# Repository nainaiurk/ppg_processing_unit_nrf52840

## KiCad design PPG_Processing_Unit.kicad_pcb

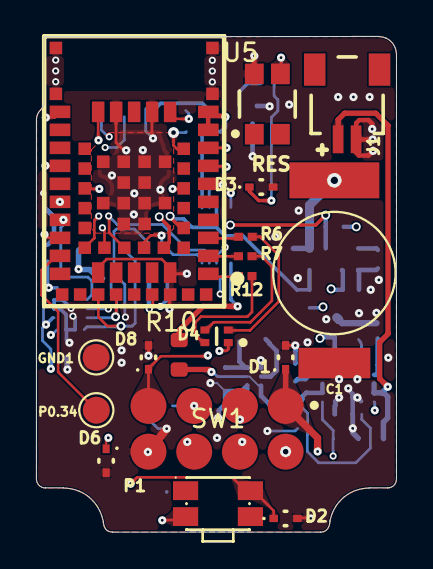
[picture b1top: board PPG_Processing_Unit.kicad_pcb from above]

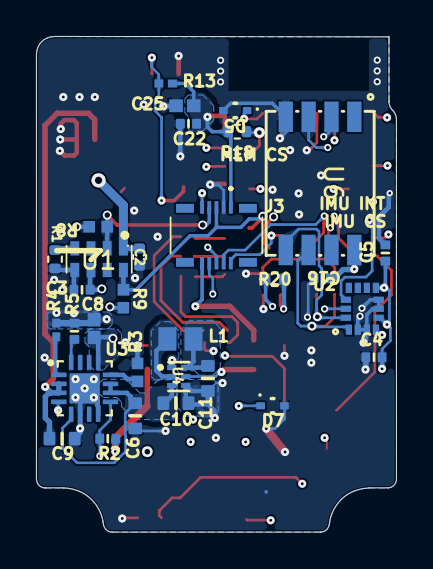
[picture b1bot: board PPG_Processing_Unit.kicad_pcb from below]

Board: 6 copper layers, 20.0 x 27.5 mm, 49 parts (31 on the bottom side), 41 nets.

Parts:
C1: .22F-SUPERCAP; DSK-RADIAL-6.8MM
C2: 0.1uF; C_0402_1005Metric
C3: Capacitor 0.1uF 0402; CAPC0402(1005)60_L
C4, C5, C16, C22: Capacitor 100nF +/-20% 25V 0402; CAPC0402(1005)60_L
C6, C9, C10, C11: Capacitor 4.7µF +/-20% 10V 0603; CAPC0603(1608)100_L
C8, C25: Capacitor 1 uF +/- 10% 6.3 V 0402; CAPC1005X55X25ML05T10
D1, D2, D3, D5, D6, D7, D8: ESD5Z3.3T1G; ONSC-SOD-523-2-502-01_V
D4: APHF1608LSEEQBDZGKC; FP-APHF1608LSEEQBDZGKC-MFG
GND1: TestPoint; TestPoint_Pad_D1.5mm
J1: SM02B-SRSS-TB(LF)(SN); FP-SM02B-SRSS-TB_LF_SN-0
J3: 51338-9873; 513389873
L1: LQM21PN2R2MGHL; FP-LQM21PH_G0-IPC_C
P0.34: TestPoint; TestPoint_Pad_D1.5mm
P1: 814-22-008-30-001101; 814-22-008-30-001101-Footprint-1
R1: 10K; R_0402_1005Metric
R2: Resistor 100K +/-1 % 0402 63 mW; RESC0402(1005)_L
R3, R8, R9: Resistor 4k7 +/-1% 0402 63 mW; RESC1005X40X25ML05T05
R4, R13: 10k; RESC1005X40X25LL05T10
R5: Resistor 12K +/-1 % 0402 63 mW; RESC0402(1005)_L
R6: 680R; RESC1005X40X25LL05T10
R7, R12: 180R; RESC1005X40X25LL05T10
R10: 0Ω; R_0603
R18: 4.7K; R_0402_1005Metric
R20: 22R; R_0402_1005Metric
SW1: EVQP7A01P; C79167_SW-SMD_EVQP7A01P
SW2: EVP-AAU02Q; FP-EVP-AAU02Q-MFG
U1: RV-3032-C7-32.768KHZ-2.5PPM-TA-QA; C5366550_DFN-8_L3_2-W1_5-P0_9-BL
U2: ISM330DHCXTR; FP-LGA-14L-DM00249496-MFG
U3: BQ24232HARGTR; QFN50P300X300X100-17N
U4: TPS62233DRYR; C2650320_SON-6_L1_5-W1_0-P0_50-BL
U5: NINA-B306; C6127317_LGA-60_L15_0-W10_0-NINA-B406-00B
U6: MKDV32GCL-STP; C7500179_LGA-8_L6_0-W8_0-P1_27-TL

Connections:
3V0: C3.2, C4.2, C5.2, C11.2, C16.2, C22.2, C25.2, D1.1 (K), D4.1 (COMMON_ANODE), J3.1, L1.2, P1.1, R2.2, R8.2, R9.2, R13.2, R18.2, SW1.2, U1.6 (VDD), U2.5 (VDDIO), U2.8 (VDD), U4.6 (FB), U5.9 (VCC_IO), U5.10 (VCC), U6.8 (VDD)
5V: C8.2, P1.2, U3.13 (IN)
/U_MCU/BATT_CE: U3.4 (~CE), U5.23 (GPIO_23/P0.29)
/U_MCU/FRAM_CS: R18.1, U5.36 (GPIO_36/P1.02), U6.2 (DAT3)
/U_MCU/GPIO: D8.1 (K), P1.7, U5.7 (GPIO_7/P0.25)
/U_MCU/IMU_CS: U2.12 (CS), U5.22 (GPIO_22/P1.13)
/U_MCU/IMU_INT: U2.4 (INT1), U5.21 (GPIO_21/P1.12)
/U_MCU/LED_BLUE: R7.2, U5.2 (GPIO_2/P0.14)
/U_MCU/LED_GREEN: R12.2, U5.1 (GPIO_1/P0.13)
/U_MCU/LED_RED: R6.2, U5.3 (GPIO_3/P0.15)
/U_MCU/MISO: U2.1 (SDO/SA0), U5.49 (GPIO_49/P0.22/QSPI_D2), U6.6 (DAT0)
/U_MCU/MOSI: U2.14 (SDA), U5.50 (GPIO_50/P0.20/QSPI_D0), U6.5 (CMD)
/U_MCU/PU_ANALOG: J3.9, U5.16 (GPIO_16/P0.03)
/U_MCU/PU_GPIO0: J3.8, U5.42 (GPIO_42/P0.26)
/U_MCU/PU_GPIO1: J3.6, U5.43 (GPIO_43/P0.06)
/U_MCU/PU_GPIO2: J3.4, U5.44 (GPIO_44/P0.27)
/U_MCU/PU_GPIO3: J3.2, U5.45 (GPIO_45/P0.07/TRACE_CLK)
/U_MCU/RESET: D3.1 (K), P1.6, R13.1, SW2.2?, U5.19 (RESET_N)
/U_MCU/SCK: R20.1, U2.13 (SCL), U5.52 (GPIO_52/P0.19/QSPI_CLK)
/U_MCU/SCL: J3.5, R9.1, U1.8 (SCL), U5.32 (GPIO_32/P0.11/TRACE_D2)
/U_MCU/SDA: J3.7, R8.1, U1.2 (SDA), U5.46 (GPIO_46/P0.12/TRACE_D1)
/U_MCU/SWCLK: D5.1 (K), P1.4, U5.11 (SWDCLK)
/U_MCU/SWDIO: D6.1 (K), P1.3, U5.15 (SWDIO)
/U_MCU/SWO: D7.1 (K), P1.5, U5.8 (GPIO_8/P1.00/TRACE_D0/SWO)
/U_MCU/USER_SWITCH: D2.1 (K), SW1.1', U5.34 (GPIO_34/P1.08)
/U_Power/CHG#: R2.1, U3.9 (~CHG), U5.39 (GPIO_39/P1.11)
/U_Sensors/VBACKUP: C1.+, C2.1, U1.1 (VBACKUP)
/U_UserInterface/BLUE: D4.3 (Blue_C), R7.1
/U_UserInterface/GREEN: D4.4 (Green_C), R12.1
/U_UserInterface/RED: D4.2 (Red_C), R6.1
GND: C1.-, C2.2, C3.1, C4.1, C5.1, C6.1, C8.1, C9.1, C10.1, C11.1, C16.1, C22.1, C25.1, D1.2 (A), D2.2 (A), D3.2 (A), D5.2 (A), D6.2 (A), D7.2 (A), D8.2 (A), GND1.1 (1_1), J1.1, J3.3, P1.8, R1.1, R3.1, R4.1, R5.1, SW2.1?, U1.5 (VSS), U2.2 (SDx), U2.3 (SCx), U2.6 (GND), U2.7 (GND), U3.6 (EN1), U3.8 (VSS), U3.17 (THERMALPAD), U4.1 (MODE), U4.4 (GND), U5.6 (GND6), U5.12 (GND12), U5.14 (GND14), U5.26 (GND26), U5.30 (GND30), U5.53 (GND53), U5.56 (EGP56), U5.57 (EGP57), U5.58 (EGP58), U5.59 (EGP59), U5.60 (EGP60), U6.4 (GND)
unnamed: C9.2, J1.2, U3.2 (BAT), U3.3 (BAT)
unnamed: J3.10, R10.1
unnamed: R1.2, U1.4 (EVI)
unnamed: R3.2, U3.12 (ILIM)
unnamed: R5.2, U3.16 (ISET)
unnamed: R4.2, U3.1 (TS)
unnamed: L1.1, U4.2 (SW)
unnamed: P0.34.1 (1_1), U5.24 (GPIO_24/P0.30)
unnamed: R20.2, U6.3 (CLK)
SYS_PWR: C6.2, C10.2, R10.2, U3.5 (EN2), U3.10 (OUT), U3.11 (OUT), U4.3 (VIN), U4.5 (EN)

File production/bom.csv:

Designator,Footprint,Quantity,Value,LCSC Part #
"C10, C11, C6, C9",CAPC0603(1608)100_L,4,Capacitor 4.7µF +/-20% 10V 0603,C389010 
"C16, C22, C4, C5",CAPC0402(1005)60_L,4,Capacitor 100nF +/-20% 25V 0402,C426067 
C2,0402,1,0.1uF,C426067 
"C25, C8",CAPC1005X55X25ML05T10,2,Capacitor 1 uF +/- 10% 6.3 V 0402,C88945 
C3,CAPC0402(1005)60_L,1,Capacitor 0.1uF 0402,C426067 
"D1, D2, D3, D5, D6, D7, D8",ONSC-SOD-523-2-502-01_V,7,ESD5Z3.3T1G,C61148
D4,FP-APHF1608LSEEQBDZGKC-MFG,1,APHF1608LSEEQBDZGKC,C3019171 
J1,FP-SM02B-SRSS-TB_LF_SN-0,1,SM02B-SRSS-TB(LF)(SN),C160402
J3,513389873,1,51338-9873,C122427 
L1,FP-LQM21PH_G0-IPC_C,1,LQM21PN2R2MGHL,C341781
R1,0402,1,10K,C25531
R10,R_0603,1,0Ω,C21189
"R12, R7",RESC1005X40X25LL05T10,2,180R,C25145
"R13, R4",RESC1005X40X25LL05T10,2,10k,C25531
R18,0402,1,4.7K,C25900
R2,RESC0402(1005)_L,1,Resistor 100K +/-1 % 0402 63 mW,C25530
R20,0402,1,22R,C25092 
"R3, R8, R9",RESC1005X40X25ML05T05,3,Resistor 4k7 +/-1% 0402 63 mW,C25900
R5,RESC0402(1005)_L,1,Resistor 12K  +/-1 % 0402 63 mW,C25752
R6,RESC1005X40X25LL05T10,1,680R,C25130
SW1,C79167_SW-SMD_EVQP7A01P,1,EVQP7A01P,C79167
SW2,FP-EVP-AAU02Q-MFG,1,EVP-AAU02Q,C79147
U1,C5366550_DFN-8_L3_2-W1_5-P0_9-BL,1,RV-3032-C7-32.768KHZ-2.5PPM-TA-QA,C5366550
U2,FP-LGA-14L-DM00249496-MFG,1,ISM330DHCXTR,C2655101
U3,QFN50P300X300X100-17N,1,BQ24232HARGTR,C2870612
U4,C2650320_SON-6_L1_5-W1_0-P0_50-BL,1,TPS62233DRYR,C2650320 
U5,C6127317_LGA-60_L15_0-W10_0-NINA-B406-00B,1,NINA-B306,C6127317
U6,C7500179_LGA-8_L6_0-W8_0-P1_27-TL,1,MKDV32GCL-STP,C7500179
